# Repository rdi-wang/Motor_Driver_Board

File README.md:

# Motor_Driver_Board
PCB for A4988 Stepper Driver + Arduino Pico

Arduino Pico pins used:
    40 - VDD
    1 - DIR
    2 - STEP
    4 - MS3
    5 - MS2
    6 - MS1

A4988 specs
- Output capacity: 35V, +-2A
- Operating voltage: 8-35V
- Continuous current per phase: 1A
- Max current per phase: 2A
- Logic voltage: 3-5.5V

A4988 Step Control
    Values in order of: MS1, MS2, MS3
        LO, LO, LO: Full step
        HI, LO, LO: 1/2 step
        LO, HI, LO: 1/4 step
        HI, HI, LO: 1/8 step
        HI, HI, HI: 1/16 step

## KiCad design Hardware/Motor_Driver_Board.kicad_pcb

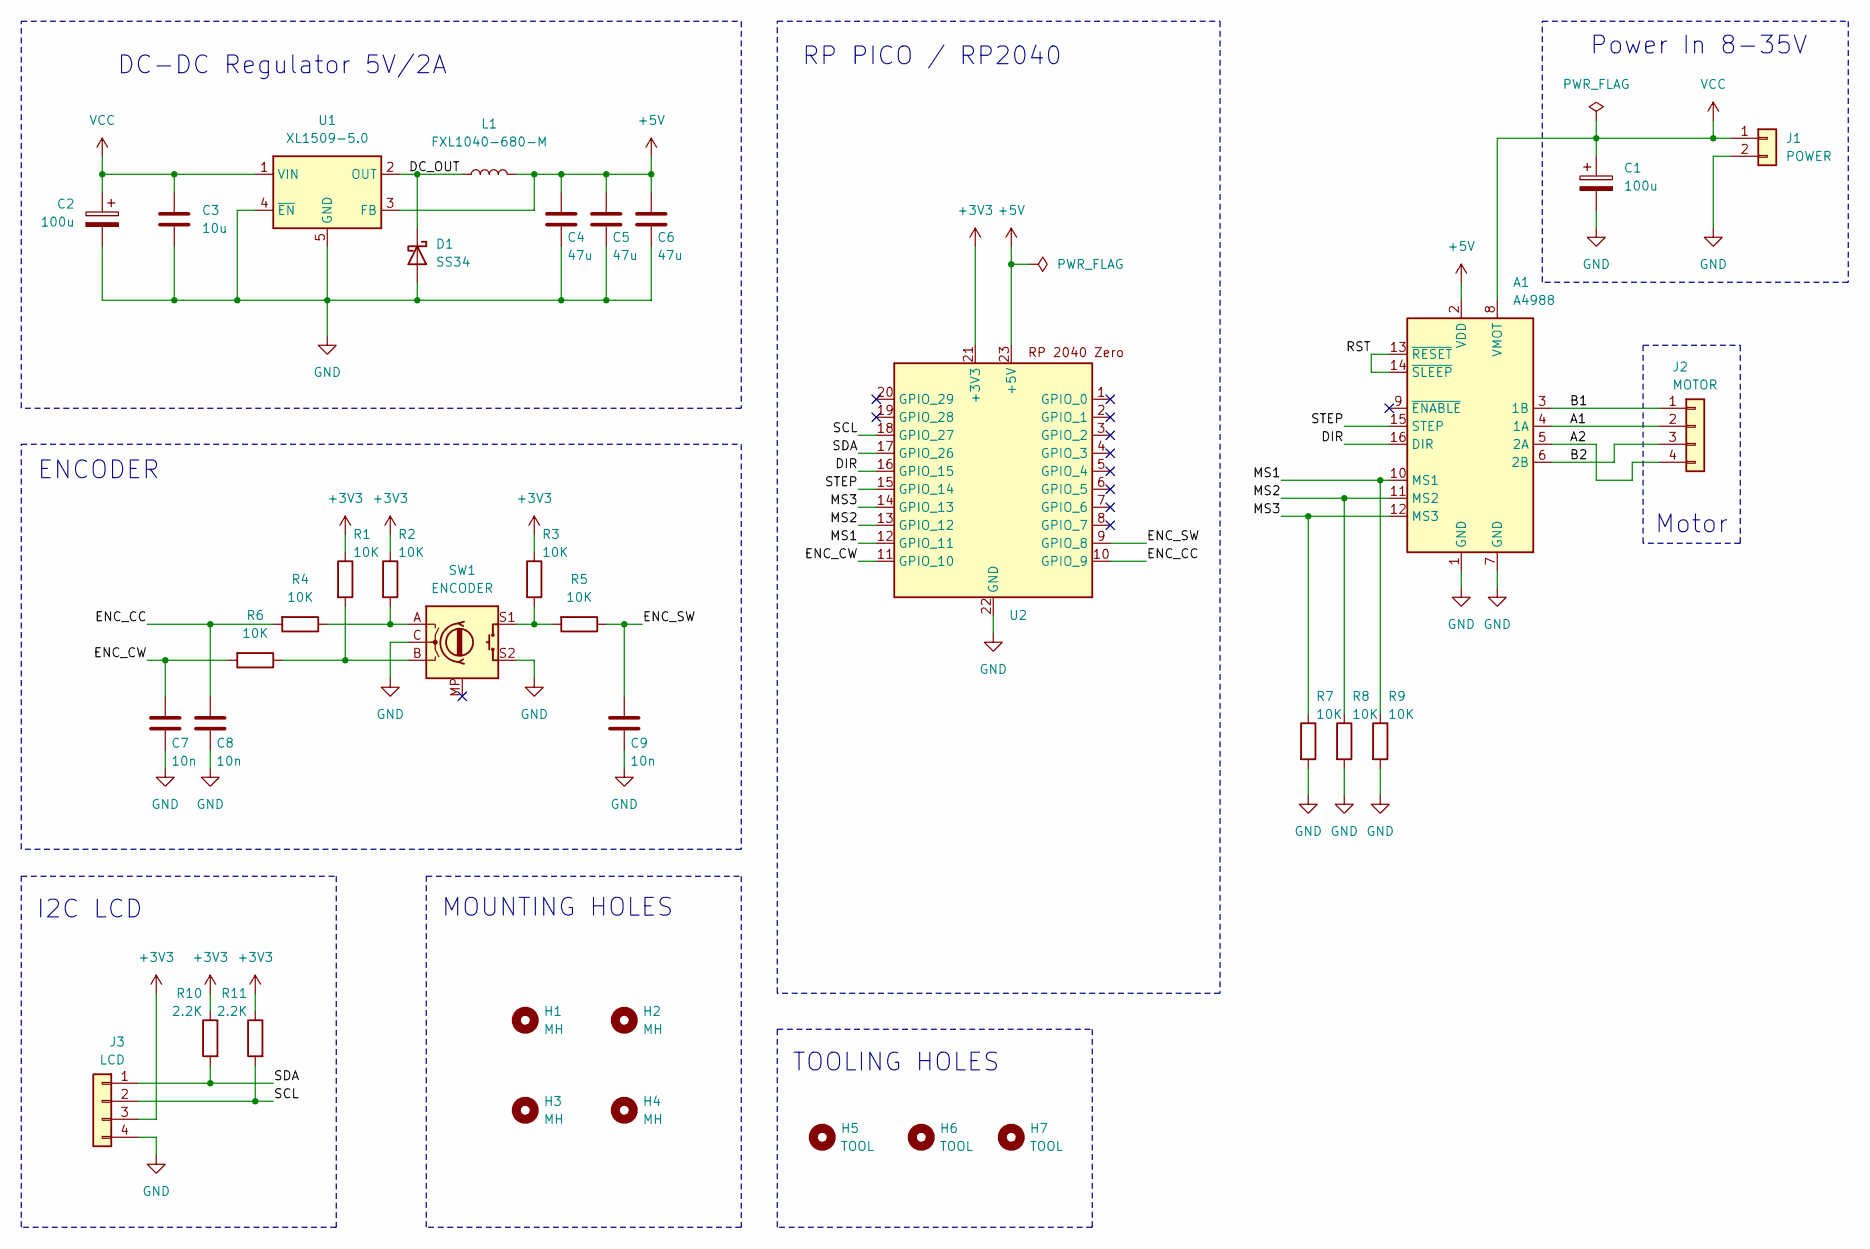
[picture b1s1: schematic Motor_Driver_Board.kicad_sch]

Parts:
A1: A4988; MODULE_A4988_STEPPER_MOTOR_DRIVER_CARRIER
C1, C2: 100u; CP_Radial_D8.0mm_P3.50mm; Manufacturer Part PA35V100M6x8; JLCPCB Part C46550435
C3: 10u; C_1206_3216Metric; Manufacturer Part CL31A106KBHNNNE; JLCPCB Part C13585
C4, C5, C6: 47u; C_1206_3216Metric; Manufacturer Part CL31A476MPHNNNE; JLCPCB Part C96123
C7, C8, C9: 10n; C_0603_1608Metric; Manufacturer Part 0603B103K500NT; JLCPCB Part C57112
D1: SS34; D_SMA; Manufacturer Part SS34; JLCPCB Part C8678
H1, H2, H3, H4: MH; MountingHole_3.2mm_M3
H5, H6, H7: TOOL; ToolingHole_1.152mm
J1: POWER; PinHeader_1x02_P2.54mm_Vertical; Manufacturer Part PZ254V-11-02P; JLCPCB Part C492401
J2: MOTOR; PinHeader_1x04_P2.54mm_Vertical; Manufacturer Part PZ254V-11-04P; JLCPCB Part C2691448
J3: LCD; PinSocket_1x04_P2.54mm_Vertical; Manufacturer Part PZ254V-11-04P; JLCPCB Part C2691448
L1: FXL1040-680-M; L_Sunlord_MWSA1005S; Manufacturer Part FXL1040-680-M; JLCPCB Part C475920
R1, R2, R3, R4, R5, R6, R7, R8, R9: 10K; R_0603_1608Metric; Manufacturer Part 0603WAF1002T5E; JLCPCB Part C25804
R10, R11: 2.2K; R_0603_1608Metric; Manufacturer Part 0603WAF1002T5E; JLCPCB Part C25804
SW1: ENCODER; RotaryEncoder_Alps_EC11E; Manufacturer Part EC11E18244AU; JLCPCB Part C202365
U1: XL1509-5.0; SOIC-8_3.9x4.9mm_P1.27mm; Manufacturer Part XL1509-5.0E1; JLCPCB Part C61063
U2: MODULE_RP2040-ZERO; Manufacturer Part RP2040-Zero; JLCPCB Part C5350143

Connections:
+3V3: J3.3, R1.1, R2.1, R3.1, R10.1, R11.1, U2.21 (+3V3)
+5V: A1.2 (VDD), C4.1, C5.1, C6.1, L1.2, U1.3 (FB), U2.23 (+5V)
/A1: A1.4 (1A), J2.2
/A2: A1.5 (2A), J2.4
/B1: A1.3 (1B), J2.1
/B2: A1.6 (2B), J2.3
/DC_OUT: D1.1 (K), L1.1, U1.2 (OUT)
/DIR: A1.16 (DIR), U2.16 (GPIO_15)
/ENC_CC: C8.1, R4.2, U2.10 (GPIO_9)
/ENC_CW: C7.1, R6.2, U2.11 (GPIO_10)
/ENC_SW: C9.1, R5.1, U2.9 (GPIO_8)
/MS1: A1.10 (MS1), R9.1, U2.12 (GPIO_11)
/MS2: A1.11 (MS2), R8.1, U2.13 (GPIO_12)
/MS3: A1.12 (MS3), R7.1, U2.14 (GPIO_13)
/RST: A1.13 (~RESET), A1.14 (~SLEEP)
/SCL: J3.2, R11.2, U2.18 (GPIO_27)
/SDA: J3.1, R10.2, U2.17 (GPIO_26)
/STEP: A1.15 (STEP), U2.15 (GPIO_14)
GND: A1.1 (GND), A1.7 (GND), C1.2, C2.2, C3.2, C4.2, C5.2, C6.2, C7.2, C8.2, C9.2, D1.2 (A), J1.2, J3.4, R7.2, R8.2, R9.2, SW1.C, SW1.S2, U1.4 (~EN), U1.5 (GND), U1.6 (GND), U1.7 (GND), U1.8 (GND), U2.22 (GND)
unnamed: R1.2, R6.1, SW1.B
unnamed: R2.2, R4.1, SW1.A
unnamed: R3.2, R5.2, SW1.S1
VCC: A1.8 (VMOT), C1.1, C2.1, C3.1, J1.1, U1.1 (VIN)

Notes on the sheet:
MOUNTING HOLES
TOOLING HOLES
I2C LCD
DC-DC Regulator 5V/2A
Motor
ENCODER
RP PICO / RP2040
Power In 8-35V

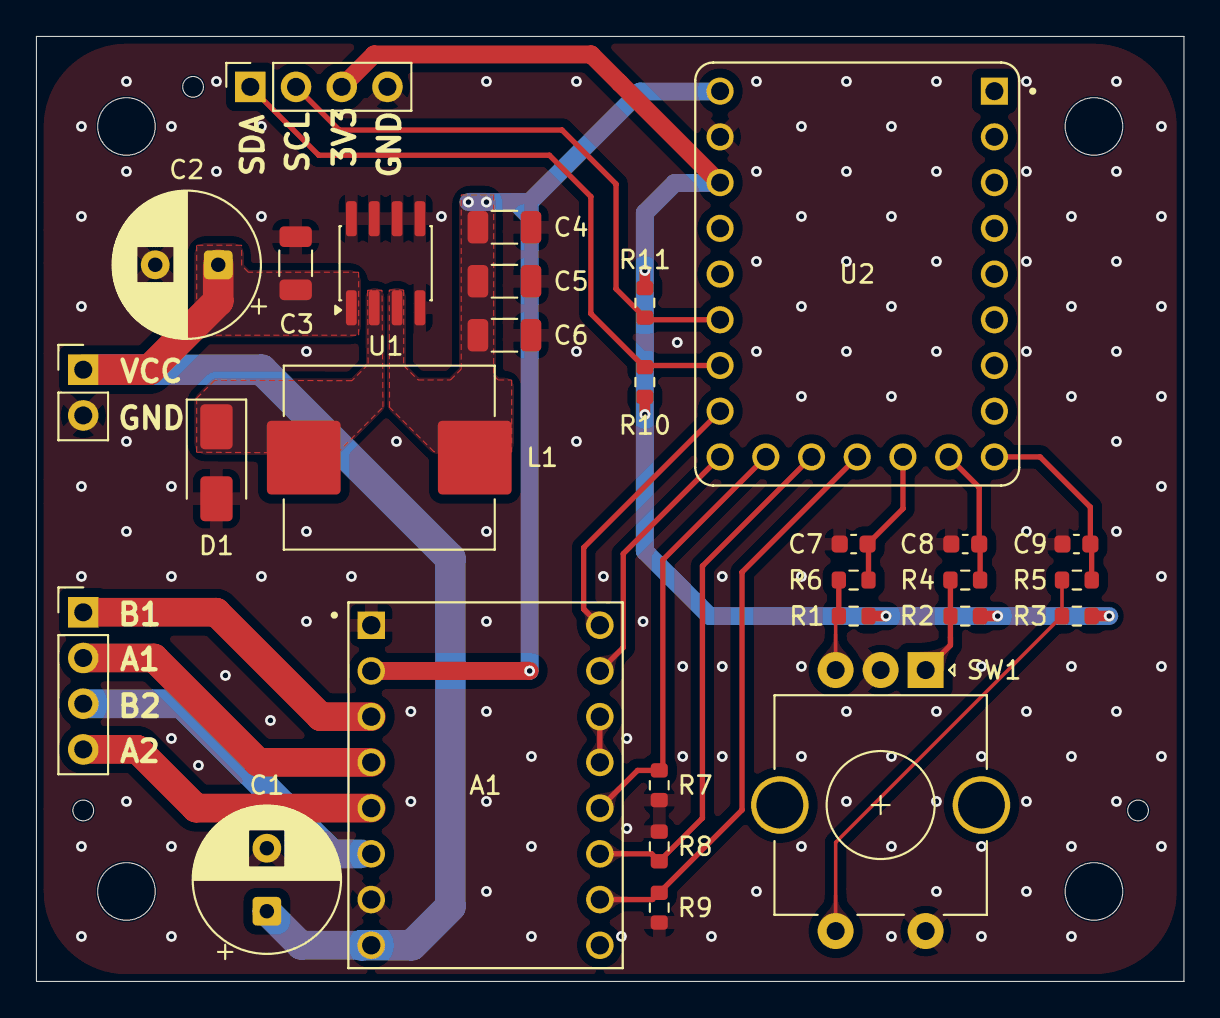
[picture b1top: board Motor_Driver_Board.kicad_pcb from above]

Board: 2 copper layers, 63.8 x 52.5 mm, 36 parts (0 on the bottom side), 23 nets.

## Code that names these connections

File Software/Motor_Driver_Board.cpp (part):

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#define GPIO_IRQ_EDGE GPIO_IRQ_EDGE_RISE

// Encoder pin definitions
#define ENC_CC 9
#define ENC_CW 10
#define ENC_SW 8

void update_display() {
    std::string step_mode;
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
void gpio_callback(uint gpio, uint32_t events) {
    // Check for clockwise operartion
    if (gpio == ENC_CW) {
        if (!gpio_get(ENC_CC)){
            stepper_set_speed_rpm(target_speed_rpm - 10.0f);

            update_display();
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    }

    // Check for counterclockwise operartion
    if (gpio == ENC_CC) {
        if (!gpio_get(ENC_CW)){
            stepper_set_speed_rpm(target_speed_rpm + 10.0f);

            update_display();
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    }

    // Check for button operation
    if (gpio == ENC_SW) {
        switch (current_microstep) {
            case MICROSTEP_FULL:
                stepper_set_microstep(MICROSTEP_HALF);
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}

static void set_gpio_handlers() {
    gpio_init(ENC_CC);
    gpio_set_dir(ENC_CC, GPIO_IN);

    gpio_init(ENC_CW);
    gpio_set_dir(ENC_CW, GPIO_IN);

    gpio_init(ENC_SW);
    gpio_set_dir(ENC_SW, GPIO_IN);

    gpio_set_irq_enabled_with_callback(ENC_CC, GPIO_IRQ_EDGE, true, gpio_callback);
    gpio_set_irq_enabled_with_callback(ENC_CW, GPIO_IRQ_EDGE, true, gpio_callback);
    gpio_set_irq_enabled_with_callback(ENC_SW, GPIO_IRQ_EDGE, true, gpio_callback);
}

int main() {
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
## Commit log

2026-04-28 Created on 4/29/2026
    Built initial schematic and PCB layout for A4988 motor controller board
    Updated readme.txt
    Updated gitignore
2026-04-28 Re-included .kicad_pro files
    Edited .gitignore to re-include .kicad_pro files, required project file
2026-04-29 Shcematic and layout
    Updated the schematic.
    Updated the layout.
2026-04-30 Switch to RP2040-Zero
    Switched controller to RP2040-Zero to save space, schematic updated.
    PCB layout in progress
2026-04-30 Added RP2040-Zero Microcontroller
    Switched previous Pi Pico to RP2040-Zero by Waveshare to reduce overall board size. Layout complete, via hatching still required
2026-04-30 Update Motor_Driver_Board.kicad_pcb
    Small update with dimensions shown in user drawings
2026-05-01 Layout revision
    Updated the schematic pinout for the RP2040.
    Updated the PCB layout.
    Rotated the motor driver.
    Moved the motor header to the side of the board.
    Added via stitching.
    Removed vias in pads.
2026-05-01 PCB layout and models
    Updated the PCB layout.
    Updated the models for the MCU, motor driver and encoder.
2026-05-04 Build outputs
    Added the intial build files.
    Added the part numbers for all components.
2026-05-04 Silkscreen notes
    Added some notes to the silkscreen layer.
2026-05-04 Footprints
    Updated the footprint for the bulk capacitors.
2026-05-04 Tooling and silkscreen
    Updated the silkscreen.
    Added tooling holes for the assembly service.
2026-05-15 Structure and software
    Updated the project structure.
    Added an initial software for the board.
    Fixed minor errors on the PCB.
2026-05-31 Schematic and acceleration
    Added an schematic of the board.
    Added an acceleration algorithm to the stepper code.
